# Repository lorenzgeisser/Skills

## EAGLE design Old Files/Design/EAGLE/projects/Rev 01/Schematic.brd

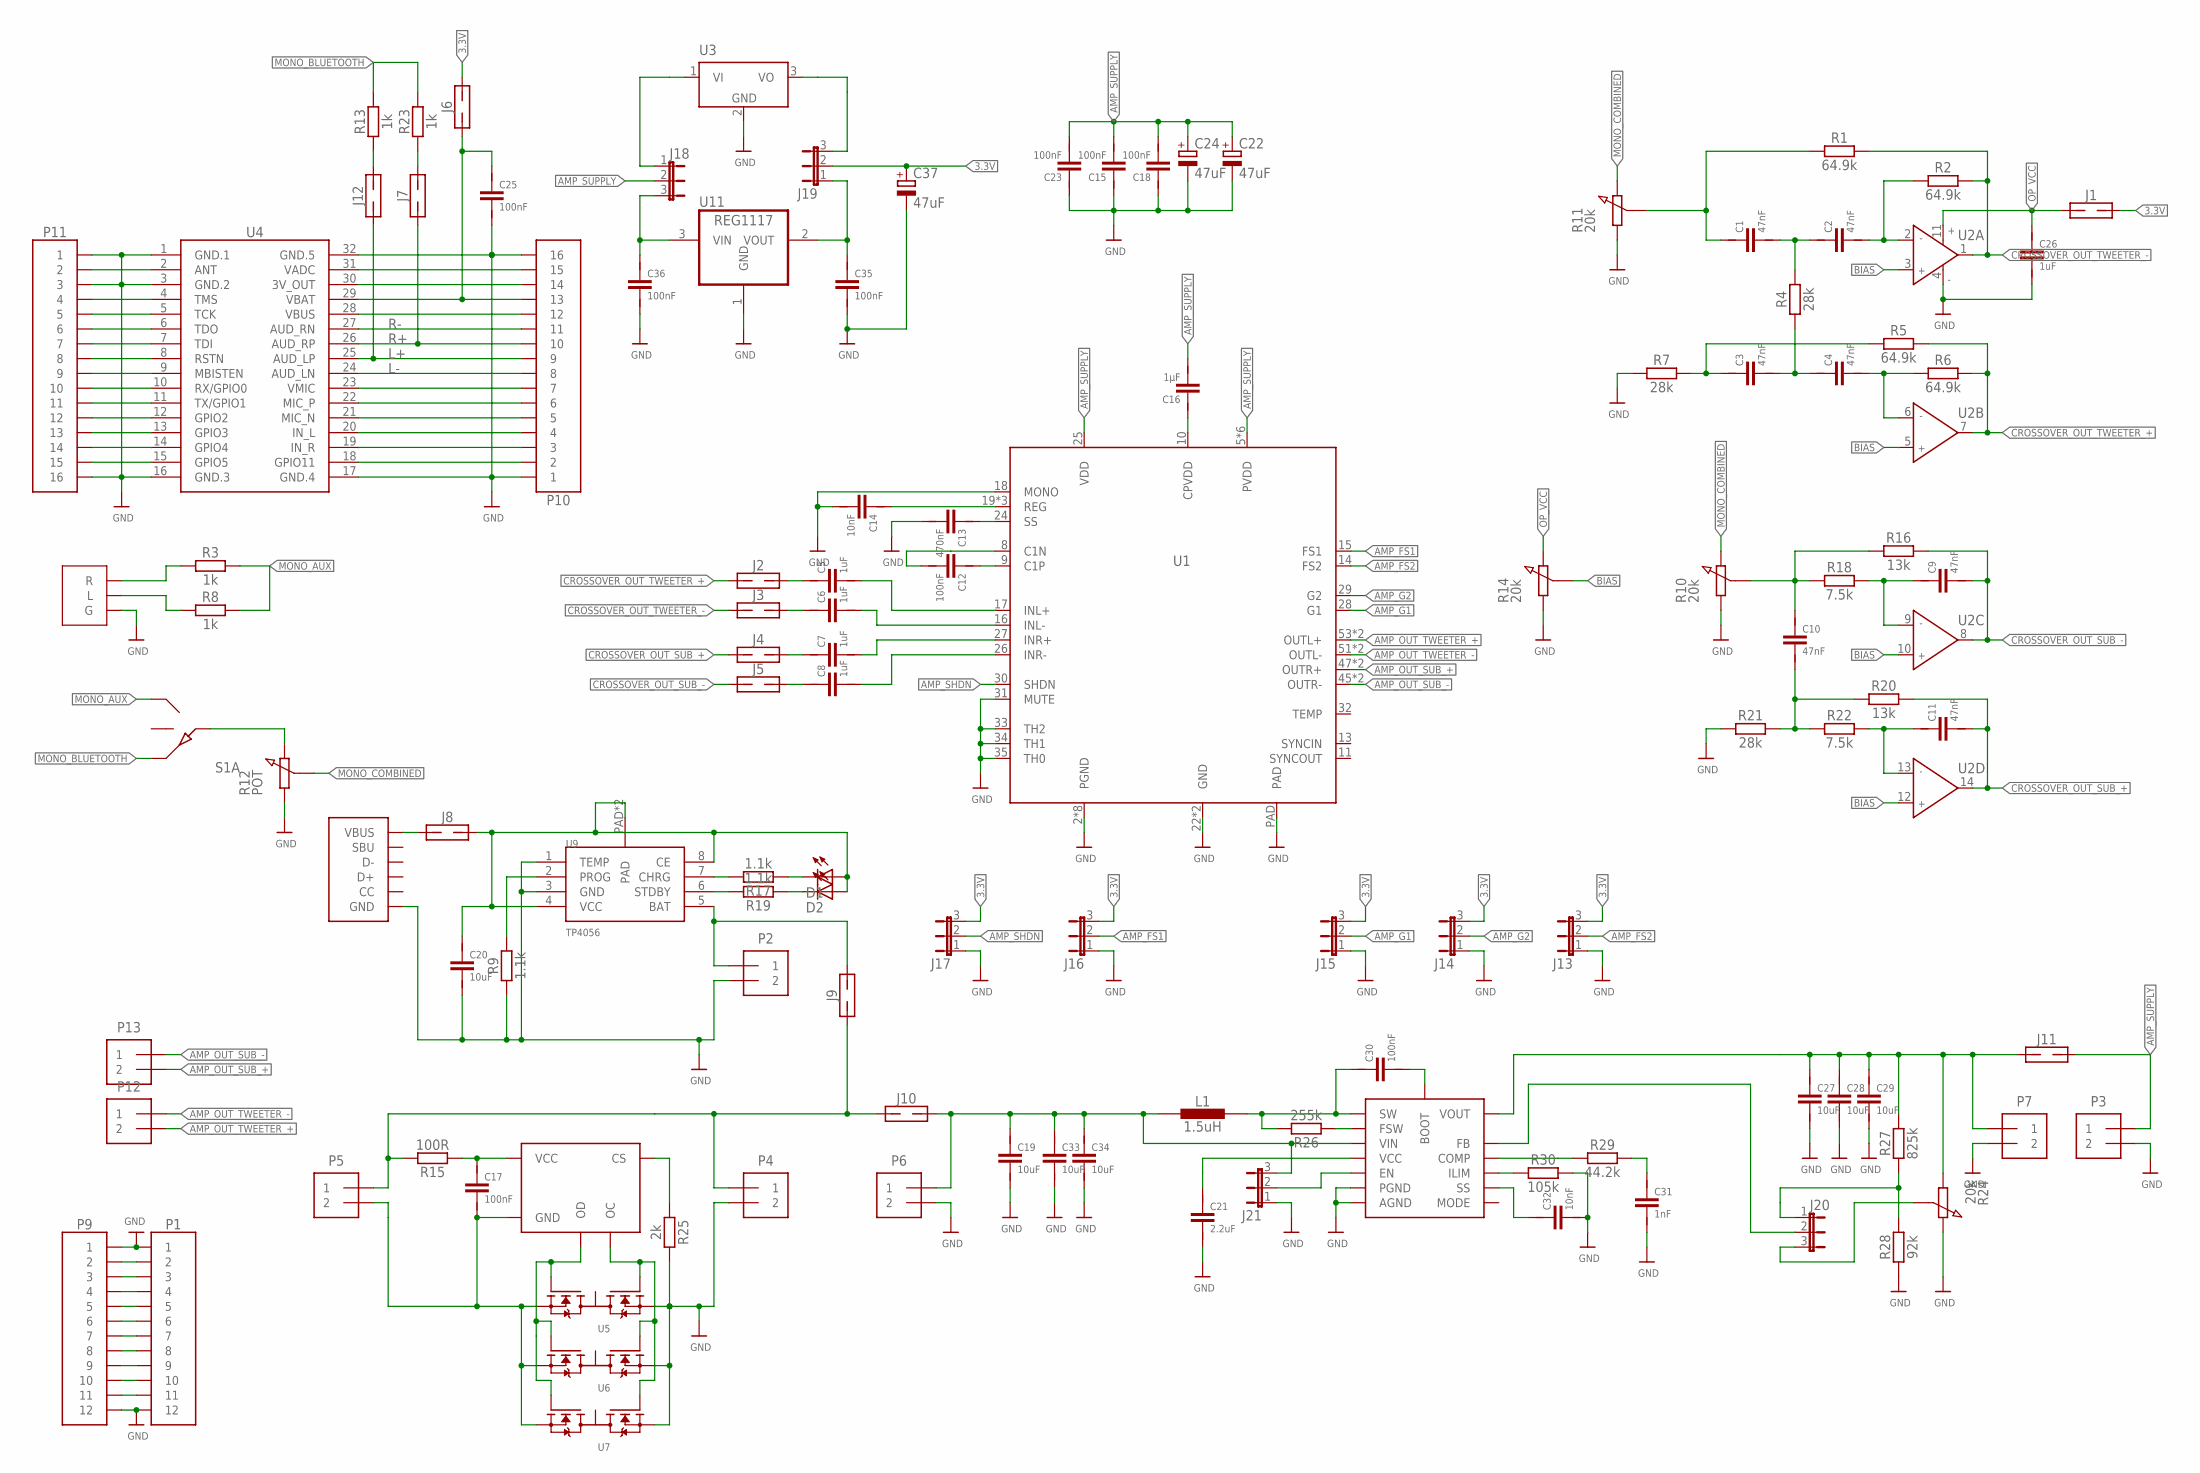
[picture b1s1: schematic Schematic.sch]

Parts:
C1, C2, C3, C4, C9, C10, C11: 47nF; R0603
C5, C6, C7, C8, C26: 1uF; R0603
C12, C15, C17, C18, C23, C25, C30, C35, C36: 100nF; R0603
C13: 470nF; R0603
C14, C32: 10nF; R0603
C16: 1µF; R0603
C19, C20, C27, C28, C29, C33, C34: 10uF; 1206
C21: 2.2uF; R0603
C22, C24, C37: 47uF; E2-4
C31: 1nF; R0603
D1, D2: LEDCHIPLED_0805; CHIPLED_0805
J1, J2, J3, J4, J5, J6, J7, J8, J9, J10, J11, J12: JUMPER_2; PIN_HEADER_2_2
J13, J14, J15, J16, J17, J18, J19, J20, J21: JP2E; JP2
L1: 1.5uH; INDUCTOR2345
P1: TYPE-_BREAKOUT; TYPE-C
P2, P3, P4, P5, P6, P7, P12, P13: HEADER_2TERM; SCREW_TERMINAL_2P
P8: AUX; AUDIO
P9: HEADER_12
P10, P11: HEADER_16
P14: TYPE-C
R1, R2, R5, R6: 64.9k; R0603
R3, R8, R13, R23: 1k; R0603
R4, R7, R21: 28k; R0603
R9, R17, R19: 1.1k; R0603
R10, R11, R14, R24: 20k; TRIMMER
R12: POT
R15: 100R; R0603
R16, R20: 13k; R0603
R18, R22: 7.5k; R0603
R25: 2k; R0603
R26: 255k; R0603
R27: 825k; R0603
R28: 92k; R0603
R29: 44.2k; R0603
R30: 105k; R0603
S1: SWITCH; FE06
U1: MAX9709; TQFN-EP
U2: MAX4478; TSSOP-14
U3: TSR12433; TSR1
U4: WIRELESS-BLUETOOTH-BK8000
U5, U6, U7: FS8205; SOP65P640X120-8N
U8: FS312F; TSOT23-6
U9: TP4056; SOP-8
U10: TPS61088; QFN50P450X350X100-21N
U11: REG1117; SOT223

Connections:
3.3V: C37.+, J1.2, J6.2, J13.3, J14.3, J15.3, J16.3, J17.3, J19.2
AMP_FS1: J16.2, U1.15 (FS1)
AMP_FS2: J13.2, U1.14 (FS2)
AMP_G1: J15.2, U1.28 (G1)
AMP_G2: J14.2, U1.29 (G2)
AMP_OUT_SUB_+: P13.P$2 (2), U1.47 (OUTR+), U1.48 (OUTR+)
AMP_OUT_SUB_-: P13.P$1 (1), U1.45 (OUTR-), U1.46 (OUTR-)
AMP_OUT_TWEETER_+: P12.P$2 (2), U1.53 (OUTL+), U1.54 (OUTL+)
AMP_OUT_TWEETER_-: P12.P$1 (1), U1.51 (OUTL-), U1.52 (OUTL-)
AMP_SHDN: J17.2, U1.30 (SHDN)
AMP_SUPPLY: C15.2, C16.2, C18.2, C22.+, C23.2, C24.+, J11.2, J18.2, P3.P$1 (1), U1.5 (PVDD), U1.6 (PVDD), U1.7 (PVDD), U1.25 (VDD), U1.36 (PVDD), U1.37 (PVDD), U1.38 (PVDD)
BIAS: R14.2, U2.3 (IN+), U2.5 (IN+), U2.10 (IN+), U2.12 (IN+)
CROSSOVER_OUT_SUB_+: C11.2, J4.1, R20.2, U2.14 (OUT)
CROSSOVER_OUT_SUB_-: C9.2, J5.1, R16.2, U2.8 (OUT)
CROSSOVER_OUT_TWEETER_+: J2.1, R5.2, R6.2, U2.7 (OUT)
CROSSOVER_OUT_TWEETER_-: J3.1, R1.2, R2.2, U2.1 (OUT)
GND: C13.2, C14.2, C15.1, C18.1, C19.2, C20.2, C21.2, C22.-, C23.1, C24.-, C25.2, C26.2, C27.2, C28.2, C29.2, C31.2, C32.2, C33.2, C34.2, C35.2, C36.2, C37.-, J13.1, J14.1, J15.1, J16.1, J17.1, J21.1, P1.A1/B12 (1), P1.B1/A12 (12), P1.P$1 (1), P1.P$2 (1), P1.P$3 (1), P1.P$4 (1), P1.P$5 (1), P1.P$6 (1), P1.P$7 (1), P1.P$8 (1), P1.P$9 (1), P1.P$10 (1), P1.P$11 (1), P1.P$12 (1), P1.P$13 (1), P1.P$14 (1), P1.P$15 (1), P1.P$16 (1), P1.P$17 (1), P1.P$18 (1), P1.P$19 (1), P1.P$20 (1), P1.P$21 (1), P1.P$22 (1), P1.P$23 (1), P1.P$24 (1), P1.P$25 (1), P1.P$26 (1), P1.P$27 (1), P1.P$28 (1), P1.P$29 (1), P1.P$30 (1), P1.P$31 (1), P1.P$32 (1), P1.P$33 (1), P1.P$34 (1), P1.P$35 (1), P1.P$36 (1), P1.P$37 (1), P1.P$38 (1), P2.P$2 (2), P3.P$2 (2), P4.P$2 (2), P6.P$2 (2), P7.P$2 (2), P8.P$3 (G), P9.1, P9.12, P10.1, P10.16, P11.1, P11.3, P11.16, P14.A1/B12 (GND), P14.B1/A12 (GND), P14.P$1 (GND), P14.P$2 (GND), P14.P$3 (GND), P14.P$4 (GND), P14.P$5 (GND), P14.P$6 (GND), P14.P$7 (GND), P14.P$8 (GND), P14.P$9 (GND), P14.P$10 (GND), P14.P$11 (GND), P14.P$12 (GND), P14.P$13 (GND), P14.P$14 (GND), P14.P$15 (GND), P14.P$16 (GND), P14.P$17 (GND), P14.P$18 (GND), P14.P$19 (GND), P14.P$20 (GND), P14.P$21 (GND), P14.P$22 (GND), P14.P$23 (GND), P14.P$24 (GND), P14.P$25 (GND), P14.P$26 (GND), P14.P$27 (GND), P14.P$28 (GND), P14.P$29 (GND), P14.P$30 (GND), P14.P$31 (GND), P14.P$32 (GND), P14.P$33 (GND), P14.P$34 (GND), P14.P$35 (GND), P14.P$36 (GND), P14.P$37 (GND), P14.P$38 (GND), R7.1, R9.1, R10.1, R11.1, R12.1, R14.1, R21.1, R24.3, R25.2, R28.1, R30.2, U1.2 (PGND), U1.3 (PGND), U1.4 (PGND), U1.18 (MONO), U1.22 (GND), U1.23 (GND), U1.31 (MUTE), U1.33 (TH2), U1.34 (TH1), U1.35 (TH0), U1.39 (PGND), U1.40 (PGND), U1.41 (PGND), U1.49 (PGND), U1.50 (PGND), U1.PAD, U2.4 (-), U3.2 (GND), U4.1 (GND.1), U4.3 (GND.2), U4.16 (GND.3), U4.17 (GND.4), U4.32 (GND.5), U5.6 (S2), U5.7 (S2), U6.6 (S2), U6.7 (S2), U7.6 (S2), U7.7 (S2), U9.1 (TEMP), U9.3 (GND), U10.20 (AGND), U10.21 (PGND), U10.22 (PGND), U11.1 (GND)
L+: J12.1, P10.9, U4.25 (AUD_LP)
L-: P10.8, U4.24 (AUD_LN)
MONO_AUX: R3.2, R8.2, S1.P$1 (1)
MONO_BLUETOOTH: R13.2, R23.2, S1.P$3 (3)
MONO_COMBINED: R10.3, R11.3, R12.2
unnamed: C5.1, J2.2
unnamed: C1.2, C2.1, R4.2
unnamed: C2.2, R2.1, U2.2 (IN-)
unnamed: C1.1, R1.1, R11.2
unnamed: C27.1, C28.1, C29.1, J11.1, P7.P$1 (1), R24.1, R27.2, U10.14 (VOUT), U10.15 (VOUT), U10.16 (VOUT)
unnamed: C4.2, R6.1, U2.6 (IN-)
unnamed: C3.2, C4.1, R4.1
unnamed: C3.1, R5.1, R7.2
unnamed: C6.1, J3.2
unnamed: C9.1, R18.2, U2.9 (IN-)
unnamed: C7.1, J4.2
unnamed: C11.1, R22.2, U2.13 (IN-)
unnamed: C10.1, R10.2, R16.1, R18.1
unnamed: C10.2, R20.1, R21.2, R22.1
unnamed: C8.1, J5.2
unnamed: C6.2, U1.16 (INL-)
unnamed: C36.1, J18.3, U11.3 (VIN)
unnamed: P8.P$1 (L), R8.1
unnamed: P8.P$2 (R), R3.1
unnamed: R12.3, S1.P$5 (C)
unnamed: C7.2, U1.27 (INR+)
unnamed: C8.2, U1.26 (INR-)
unnamed: C5.2, U1.17 (INL+)
unnamed: C12.2, U1.8 (C1N)
unnamed: C12.1, U1.9 (C1P)
unnamed: C13.1, U1.24 (SS)
unnamed: P1.A4/B9 (2), P9.2
unnamed: C14.1, U1.19 (REG), U1.20 (REG), U1.21 (REG)
unnamed: P1.B8 (3), P9.3
unnamed: P1.A5 (4), P9.4
unnamed: P1.B7 (5), P9.5
unnamed: P1.A6 (6), P9.6
unnamed: P1.A7 (7), P9.7
unnamed: C16.1, U1.10 (CPVDD)
unnamed: U5.5 (G2), U6.5 (G2), U7.5 (G2), U8.3 (OC)
unnamed: C20.1, D1.A, D2.A, J8.2, U9.4 (VCC), U9.8 (CE), U9.PAD, U9.PAD2 (PAD)
unnamed: R9.2, U9.2 (PROG)
unnamed: J19.3, U3.3 (VO)
unnamed: R17.2, U9.7 (CHRG)
unnamed: R19.2, U9.6 (STDBY)
unnamed: D1.C, R17.1
unnamed: D2.C, R19.1
unnamed: J9.2, P2.P$1 (1), U9.5 (BAT)
unnamed: J8.1, P14.A4/B9 (VBUS), P14.B4/A9 (VBUS)
unnamed: R26.1, U10.3 (FSW)
unnamed: P1.B6 (8), P9.8
unnamed: P1.A8 (9), P9.9
unnamed: P1.B5 (10), P9.10
unnamed: P1.B4/A9 (11), P9.11
unnamed: C35.1, J19.1, U11.2 (VOUT)
unnamed: R25.1, U8.2 (CS)
unnamed: C17.1, R15.1, U8.5 (VCC)
unnamed: C17.2, P5.P$2 (2), U5.2 (S1), U5.3 (S1), U6.2 (S1), U6.3 (S1), U7.2 (S1), U7.3 (S1), U8.6 (GND)
unnamed: J9.1, J10.1, P4.P$1 (1), P5.P$1 (1), R15.2
unnamed: U5.4 (G1), U6.4 (G1), U7.4 (G1), U8.1 (OD)
unnamed: C30.1, L1.P$2 (2), R26.2, U10.4 (SW), U10.5 (SW), U10.6 (SW), U10.7 (SW)
unnamed: C30.2, U10.8 (BOOT)
unnamed: C21.1, U10.1 (VCC)
unnamed: C19.1, C33.1, C34.1, J10.2, J21.3, L1.P$1 (1), P6.P$1 (1), U10.9 (VIN)
unnamed: J21.2, U10.2 (EN)
unnamed: R30.1, U10.19 (ILIM)
unnamed: R29.1, U10.18 (COMP)
unnamed: C31.1, R29.2
unnamed: J20.2, U10.17 (FB)
unnamed: C32.1, U10.10 (SS)
unnamed: J20.1, R27.1, R28.2
unnamed: J20.3, R24.2
unnamed: P10.2, U4.18 (GPIO11)
unnamed: P10.3, U4.19 (IN_R)
unnamed: P10.4, U4.20 (IN_L)
unnamed: P10.5, U4.21 (MIC_N)
unnamed: P10.6, U4.22 (MIC_P)
unnamed: P10.7, U4.23 (VMIC)
unnamed: P10.12, U4.28 (VBUS)
unnamed: C25.1, J6.1, P10.13, U4.29 (VBAT)
unnamed: P10.14, U4.30 (3V_OUT)
unnamed: P10.15, U4.31 (VADC)
unnamed: P11.2, U4.2 (ANT)
unnamed: P11.4, U4.4 (TMS)
unnamed: P11.5, U4.5 (TCK)
unnamed: P11.6, U4.6 (TDO)
unnamed: P11.7, U4.7 (TDI)
unnamed: P11.8, U4.8 (RSTN)
unnamed: P11.9, U4.9 (MBISTEN)
unnamed: P11.10, U4.10 (RX/GPIO0)
unnamed: P11.11, U4.11 (TX/GPIO1)
unnamed: P11.12, U4.12 (GPIO2)
unnamed: P11.13, U4.13 (GPIO3)
unnamed: P11.14, U4.14 (GPIO4)
unnamed: P11.15, U4.15 (GPIO5)
unnamed: J7.2, R23.1
unnamed: J12.2, R13.1
OP_VCC: C26.1, J1.1, R14.3, U2.11 (+)
R+: J7.1, P10.10, U4.26 (AUD_RP)
R-: P10.11, U4.27 (AUD_RN)
VI: J18.1, U3.1 (VI)

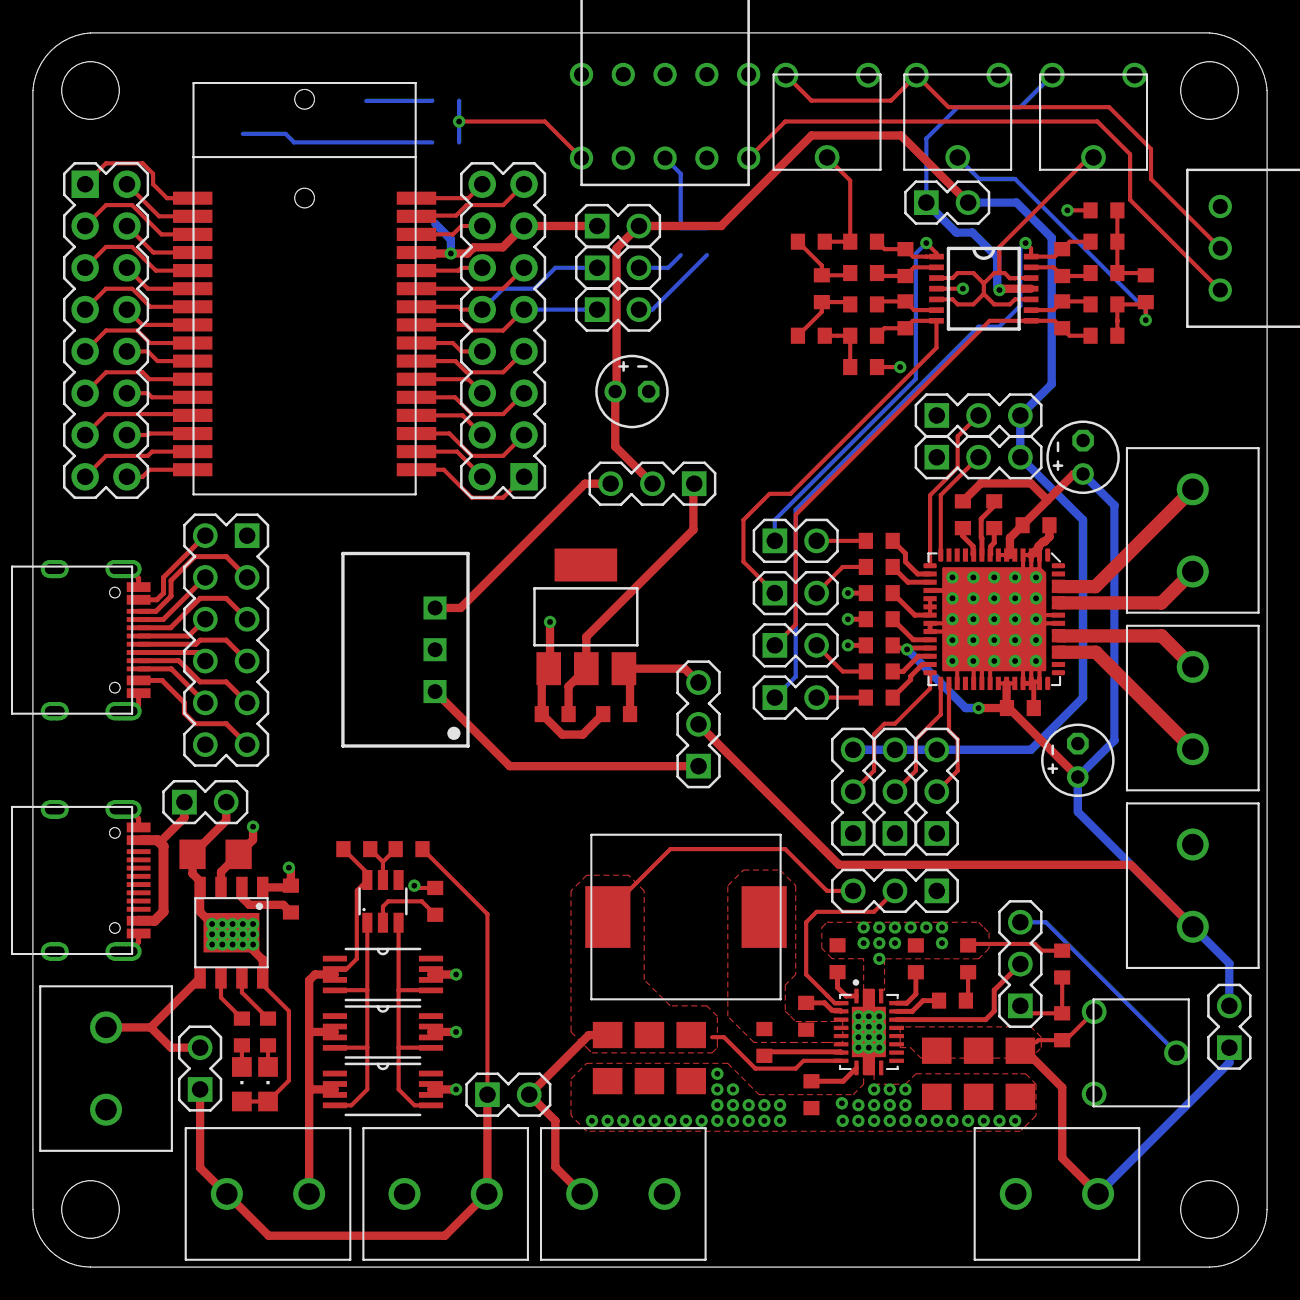
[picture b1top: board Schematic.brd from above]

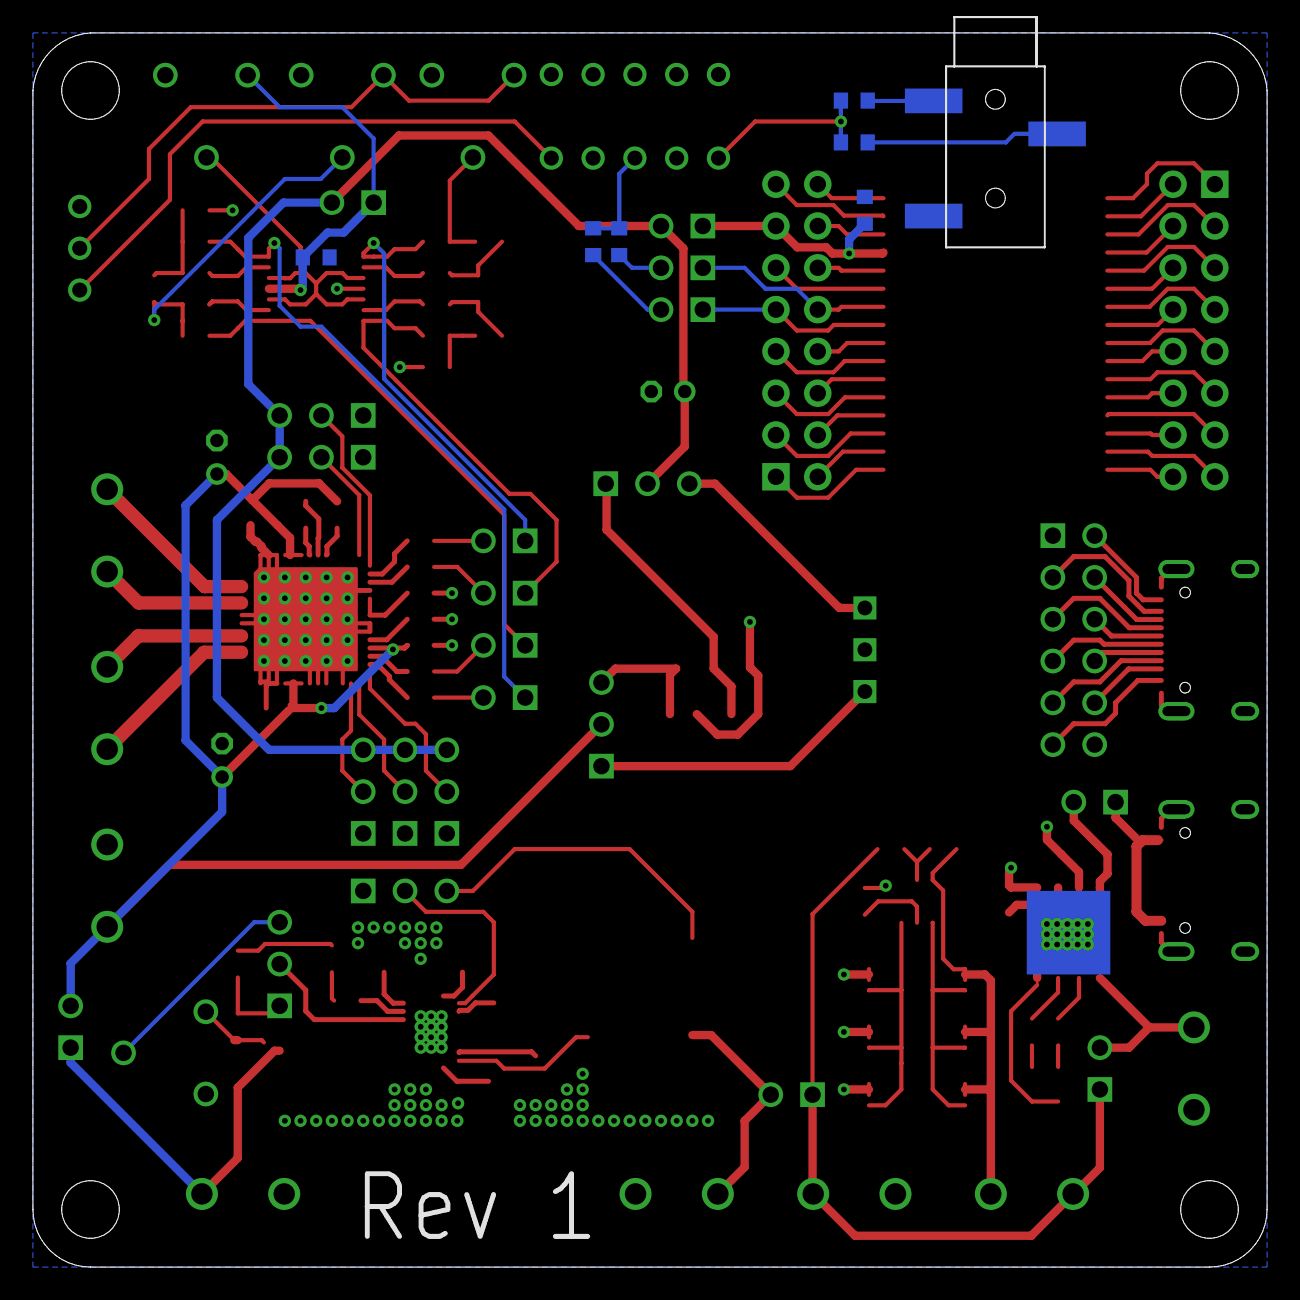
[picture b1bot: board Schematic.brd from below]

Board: 2 copper layers, 75.0 x 75.0 mm, 117 parts (7 on the bottom side), 118 nets.

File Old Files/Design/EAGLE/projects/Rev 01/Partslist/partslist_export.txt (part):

Partlist

Exported from Schematic.sch at 8/4/2018 7:06 PM

EAGLE Version 9.1.1 Copyright (c) 1988-2018 Autodesk, Inc.

Assembly variant: 

Part     Value                     Device                    Package                   Library    Sheet

C1       47nF                      CAPACITOR                 R0603                     Schematic  1
C2       47nF                      CAPACITOR                 R0603                     Schematic  1
C3       47nF                      CAPACITOR                 R0603                     Schematic  1
C4       47nF                      CAPACITOR                 R0603                     Schematic  1
C5       1uF                       CAPACITOR                 R0603                     Schematic  1
C6       1uF                       CAPACITOR                 R0603                     Schematic  1
C7       1uF                       CAPACITOR                 R0603                     Schematic  1
C8       1uF                       CAPACITOR                 R0603                     Schematic  1
C9       47nF                      CAPACITOR                 R0603                     Schematic  1
C10      47nF                      CAPACITOR                 R0603                     Schematic  1
C11      47nF                      CAPACITOR                 R0603                     Schematic  1
C12      100nF                     CAPACITOR                 R0603                     Schematic  1
C13      470nF                     CAPACITOR                 R0603                     Schematic  1
C14      10nF                      CAPACITOR                 R0603                     Schematic  1
C15      100nF                     CAPACITOR                 R0603                     Schematic  1
C16      1µF                       CAPACITOR                 R0603                     Schematic  1
C17      100nF                     CAPACITOR                 R0603                     Schematic  1
C18      100nF                     CAPACITOR                 R0603                     Schematic  1
C19      10uF                      CAPACITOR1206             1206                      Schematic  1
C20      10uF                      CAPACITOR1206             1206                      Schematic  1
C21      2.2uF                     CAPACITOR                 R0603                     Schematic  1
C22      47uF                      CPOL-EUE2-4               E2-4                      Schematic  1
C23      100nF                     CAPACITOR                 R0603                     Schematic  1
C24      47uF                      CPOL-EUE2-4               E2-4                      Schematic  1
C25      100nF                     CAPACITOR                 R0603                     Schematic  1
C26      1uF                       CAPACITOR                 R0603                     Schematic  1
C27      10uF                      CAPACITOR1206             1206                      Schematic  1
C28      10uF                      CAPACITOR1206             1206                      Schematic  1
C29      10uF                      CAPACITOR1206             1206                      Schematic  1
C30      100nF                     CAPACITOR                 R0603                     Schematic  1
C31      1nF                       CAPACITOR                 R0603                     Schematic  1
C32      10nF                      CAPACITOR                 R0603                     Schematic  1
C33      10uF                      CAPACITOR1206             1206                      Schematic  1
C34      10uF                      CAPACITOR1206             1206                      Schematic  1
C35      100nF                     CAPACITOR                 R0603                     Schematic  1
C36      100nF                     CAPACITOR                 R0603                     Schematic  1
C37      47uF                      CPOL-EUE2-4               E2-4                      Schematic  1
D1                                 LEDCHIPLED_0805           CHIPLED_0805              Schematic  1
D2                                 LEDCHIPLED_0805           CHIPLED_0805              Schematic  1
J1       JUMPER_2                  JUMPER_2                  PIN_HEADER_2_2            Schematic  1
J2       JUMPER_2                  JUMPER_2                  PIN_HEADER_2_2            Schematic  1
J3       JUMPER_2                  JUMPER_2                  PIN_HEADER_2_2            Schematic  1
J4       JUMPER_2                  JUMPER_2                  PIN_HEADER_2_2            Schematic  1
J5       JUMPER_2                  JUMPER_2                  PIN_HEADER_2_2            Schematic  1
J6       JUMPER_2                  JUMPER_2                  PIN_HEADER_2_2            Schematic  1
J7       JUMPER_2                  JUMPER_2                  PIN_HEADER_2_2            Schematic  1
J8       JUMPER_2                  JUMPER_2                  PIN_HEADER_2_2            Schematic  1
J9       JUMPER_2                  JUMPER_2                  PIN_HEADER_2_2            Schematic  1
J10      JUMPER_2                  JUMPER_2                  PIN_HEADER_2_2            Schematic  1
J11      JUMPER_2                  JUMPER_2                  PIN_HEADER_2_2            Schematic  1
J12      JUMPER_2                  JUMPER_2                  PIN_HEADER_2_2            Schematic  1
J13                                JP2E                      JP2                       Schematic  1
J14                                JP2E                      JP2                       Schematic  1
J15                                JP2E                      JP2                       Schematic  1
J16                                JP2E                      JP2                       Schematic  1
J17                                JP2E                      JP2                       Schematic  1
J18                                JP2E                      JP2                       Schematic  1
J19                                JP2E                      JP2                       Schematic  1
J20                                JP2E                      JP2                       Schematic  1
J21                                JP2E                      JP2                       Schematic  1
L1       1.5uH                     INDUCTOR6519              INDUCTOR2345              Schematic  1
P1       TYPE-_BREAKOUT            TYPE-_BREAKOUT            TYPE-C                    Schematic  1
P2       HEADER_2TERM              HEADER_2TERM              SCREW_TERMINAL_2P         Schematic  1
P3       HEADER_2TERM              HEADER_2TERM              SCREW_TERMINAL_2P         Schematic  1
P4       HEADER_2TERM              HEADER_2TERM              SCREW_TERMINAL_2P         Schematic  1
P5       HEADER_2TERM              HEADER_2TERM              SCREW_TERMINAL_2P         Schematic  1
P6       HEADER_2TERM              HEADER_2TERM              SCREW_TERMINAL_2P         Schematic  1
P7       HEADER_2TERM              HEADER_2TERM              SCREW_TERMINAL_2P         Schematic  1
P8       AUX                       AUX                       AUDIO                     Schematic  1
P9       HEADER_12                 HEADER_12                 HEADER_12                 Schematic  1
P10      HEADER_16                 HEADER_16                 HEADER_16                 Schematic  1
P11      HEADER_16                 HEADER_16                 HEADER_16                 Schematic  1
P12      HEADER_2TERM              HEADER_2TERM              SCREW_TERMINAL_2P         Schematic  1
P13      HEADER_2TERM              HEADER_2TERM              SCREW_TERMINAL_2P         Schematic  1
P14      TYPE-C                    TYPE-C                    TYPE-C                    Schematic  1
R1       64.9k                     RESISTOR0603              R0603                     Schematic  1
R2       64.9k                     RESISTOR0603              R0603                     Schematic  1
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
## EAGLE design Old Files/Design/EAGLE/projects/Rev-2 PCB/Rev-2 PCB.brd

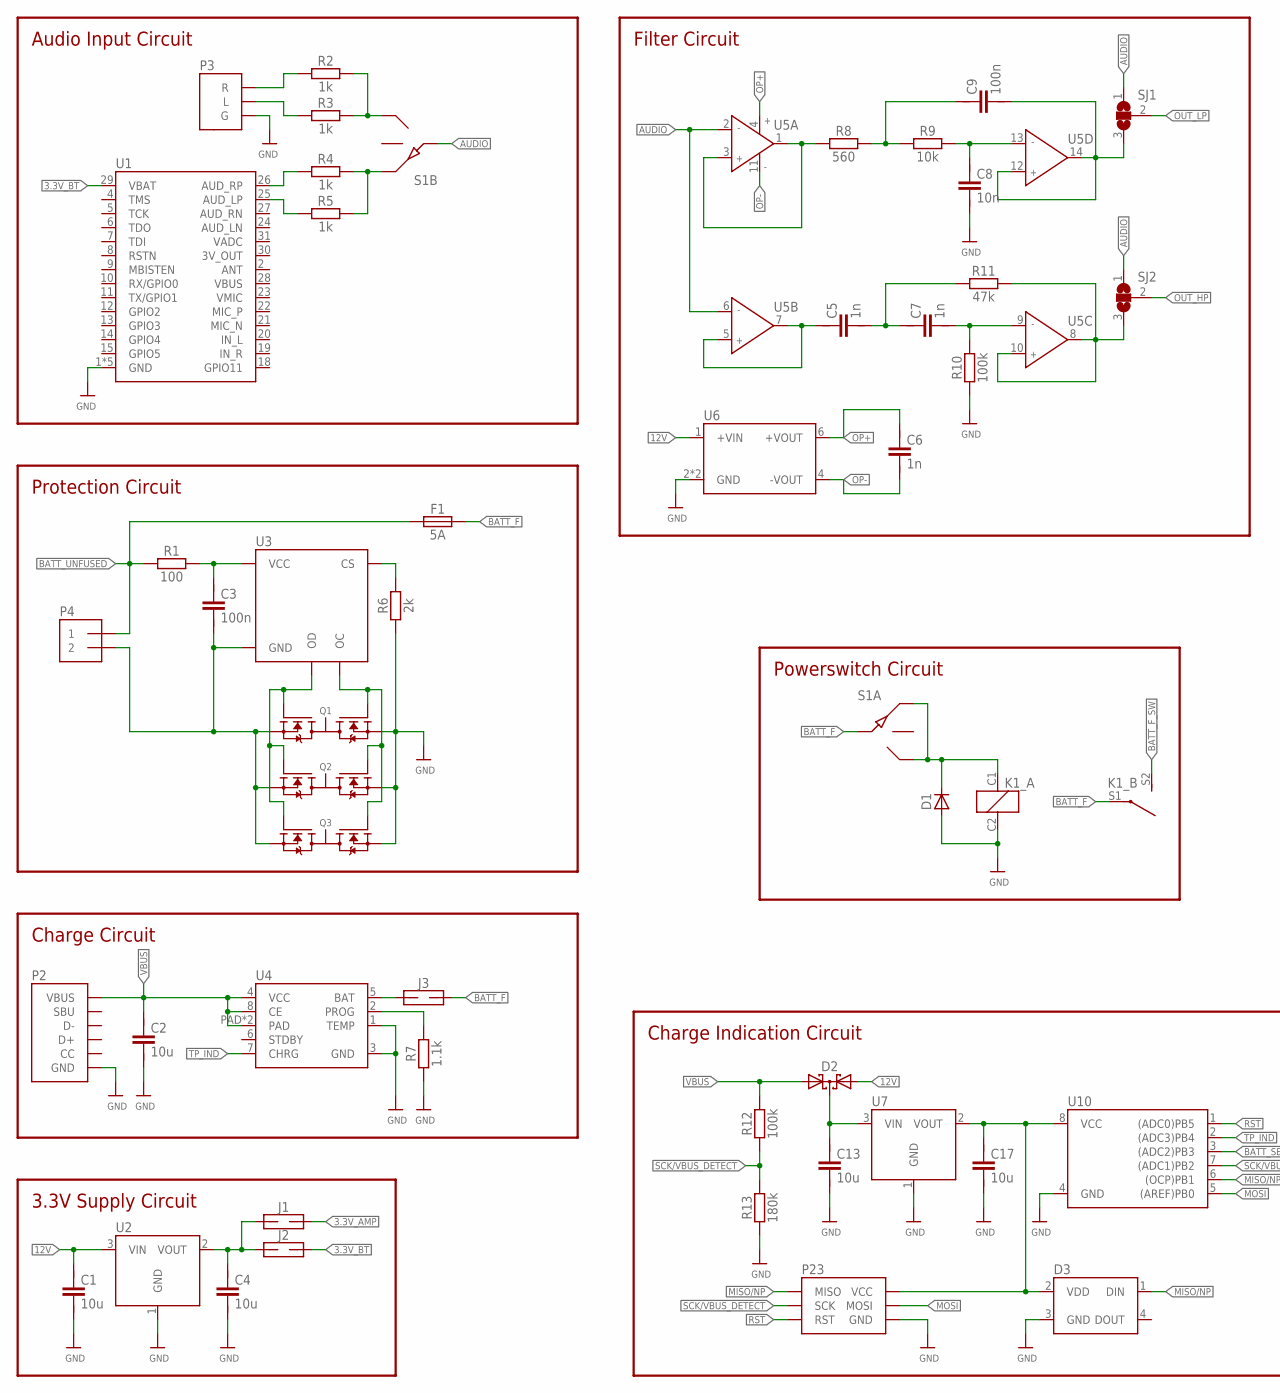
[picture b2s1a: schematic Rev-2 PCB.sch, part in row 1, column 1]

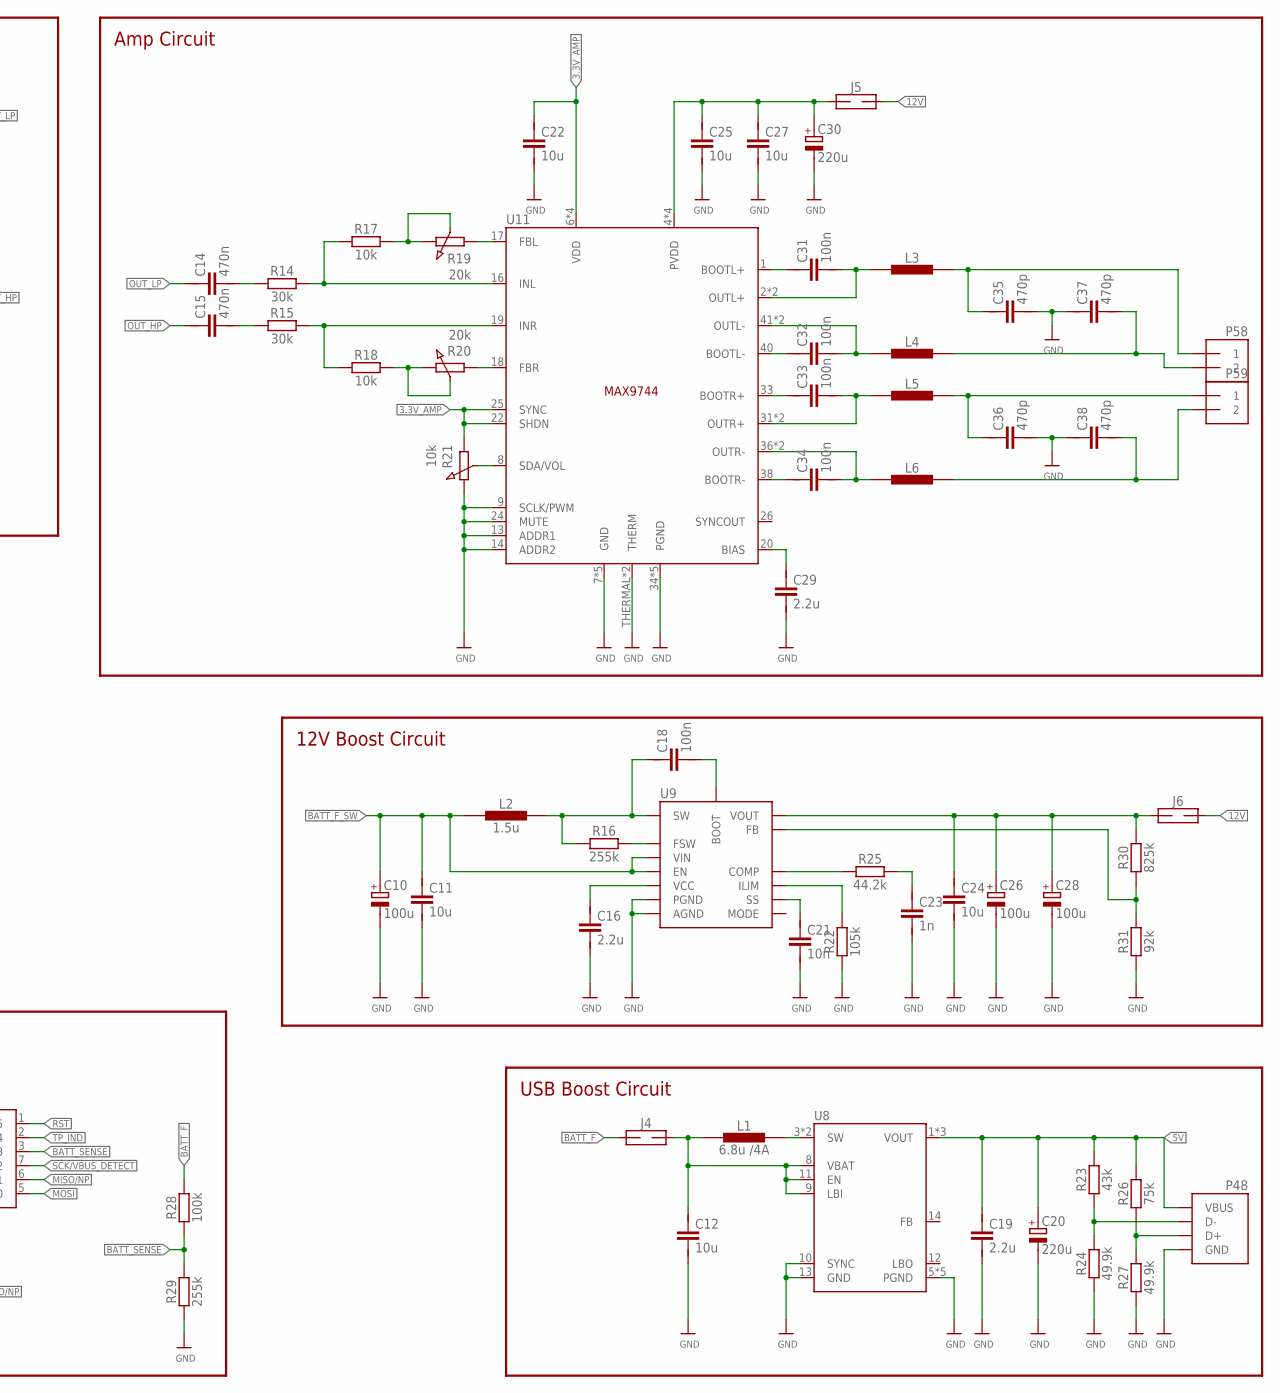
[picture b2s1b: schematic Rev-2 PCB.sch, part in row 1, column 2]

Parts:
C1, C4, C13, C17: 10u; R0603
C2, C11, C12, C22, C24, C25, C27: 10u; 1206
C3, C9, C18: 100n; R0603
C5, C6, C7, C23: 1n; R0603
C8, C21: 10n; R0603
C10, C26, C28: 100u; UD-6,3X7,7_NICHICON
C14, C15: 470n; R0603
C16, C19, C29: 2.2u; R0603
C20, C30: 220u; UD-6,3X7,7_NICHICON
C31, C32, C33, C34: 100n; 0805
C35, C36, C37, C38: 470p; 0805
D1: DIODEDO-214AC; DO214AC
D2: BAS70-05; SOT23
D3: NEOPIXEL; LED-RGB-THRU
F1: 5A; FUSE_SMD
J1, J2, J3, J4, J5, J6: JUMPER_2S; SJ
K1: RELAY_2; RELAY
L1: 6.8u /4A; INDUCTOR234545
L2: 1.5u; INDUCTOR2345
L3, L4, L5, L6: INDUCTOR0805; 0805
P2: USB_TYPE-C; TYPE-C
P3: AUX; AUDIO
P4, P58, P59: HEADER_2MOLEX; MOLEX_43650_2P
P23: SPI-HEADERNS; 2X3-NS
P48: USB_TYPE-A; USB-A
Q1, Q2, Q3: FS8205; SOP65P640X120-8N
R1: 100; R0603
R2, R3, R4, R5: 1k; R0603
R6: 2k; R0603
R7: 1.1k; R0603
R8: 560; R0603
R9, R17, R18: 10k; R0603
R10, R12, R28: 100k; R0603
R11: 47k; R0603
R13: 180k; R0603
R14, R15: 30k; R0603
R16, R29: 255k; R0603
R19, R20: 20k; TRIMMPOTI
R21: 10k; POT
R22: 105k; R0603
R23: 43k; R0603
R24, R27: 49.9k; R0603
R25: 44.2k; R0603
R26: 75k; R0603
R30: 825k; R0603
R31: 92k; R0603
S1: SWITCH; FE06
SJ1, SJ2: SJ2W; SJ_2
U1: BK8000; WIRELESS-BLUETOOTH-BK8000
U2, U7: REG1118SOT23-3; SOT23
U3: FS312F; TSOT23-6
U4: TP4056; SOP-8
U5: QUAD_OP; SO14
U6: NMA; CONV_PCN2-S24-D15-S
U8: TPS6103X; PVQFN-16
U9: TPS61088; QFN50P450X350X100-21N
U10: TINY15LS; SOIC8
U11: MAX9744; TQFN44_7MM

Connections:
3.3V_AMP: C22.1, J1.2, R21.1, U11.6 (VDD), U11.10 (VDD), U11.21 (VDD), U11.22 (SHDN), U11.25 (SYNC), U11.28 (VDD)
3.3V_BT: J2.2, U1.29 (VBAT)
3V_OUT: U1.30 (3V_OUT)
5V: C19.1, C20.+, P48.VBUS, R23.2, R26.2, U8.1 (VOUT), U8.15 (VOUT), U8.16 (VOUT)
12V: C1.1, D2.1 (A1), J5.2, J6.2, U2.3 (VIN), U6.1 (+VIN)
12V_AMP: C25.1, C27.1, C30.+, J5.1, U11.4 (PVDD), U11.5 (PVDD), U11.29 (PVDD), U11.30 (PVDD)
AUDIO: S1.P$6 (C), SJ1.1, SJ2.1, U5.2 (IN-), U5.6 (IN-)
BATT_F: F1.2 (4), J3.2, J4.1, K1.S1 (MITTE), R28.2, S1.P$5 (C)
BATT_F_SW: C10.+, C11.1, K1.S2 (OFF), L2.P$1 (1), U9.2 (EN), U9.9 (VIN)
BATT_SENSE: R28.1, R29.2, U10.3 ((ADC2)PB3)
BATT_UNFUSED: F1.1 (3), P4.1, R1.1
GND: C1.2, C2.2, C4.2, C8.2, C10.-, C11.2, C12.2, C13.2, C16.2, C17.2, C19.2, C20.-, C21.2, C22.2, C23.2, C24.2, C25.2, C26.-, C27.2, C28.-, C29.2, C30.-, C35.2, C36.2, C37.1, C38.1, D1.A, D3.3 (GND), K1.C2 (2), P2.A1/B12 (GND), P2.B1/A12 (GND), P2.P$1 (GND), P2.P$2 (GND), P2.P$3 (GND), P2.P$4 (GND), P2.P$5 (GND), P2.P$6 (GND), P2.P$7 (GND), P2.P$8 (GND), P2.P$9 (GND), P2.P$10 (GND), P2.P$11 (GND), P2.P$12 (GND), P2.P$13 (GND), P2.P$14 (GND), P2.P$15 (GND), P2.P$16 (GND), P2.P$17 (GND), P2.P$18 (GND), P2.P$19 (GND), P2.P$20 (GND), P2.P$21 (GND), P2.P$22 (GND), P2.P$23 (GND), P2.P$24 (GND), P2.P$25 (GND), P2.P$26 (GND), P2.P$27 (GND), P2.P$28 (GND), P2.P$29 (GND), P2.P$30 (GND), P2.P$31 (GND), P2.P$32 (GND), P2.P$33 (GND), P2.P$34 (GND), P2.P$35 (GND), P2.P$36 (GND), P2.P$37 (GND), P2.P$38 (GND), P3.P$3 (G), P23.6 (GND), P48.GND, P48.S1 (GND), P48.S2 (GND), P48.S3 (GND), P48.S4 (GND), Q1.6 (S2), Q1.7 (S2), Q2.6 (S2), Q2.7 (S2), Q3.6 (S2), Q3.7 (S2), R6.1, R7.1, R10.1, R13.1, R21.3, R22.1, R24.1, R27.1, R29.1, R31.1, U1.1 (GND), U1.3 (GND), U1.16 (GND), U1.17 (GND), U1.32 (GND), U2.1 (GND), U4.1 (TEMP), U4.3 (GND), U6.2 (GND), U6.5 (GND), U7.1 (GND), U8.5 (PGND), U8.6 (PGND), U8.7 (PGND), U8.10 (SYNC), U8.13 (GND), U8.THERMAL (PGND), U8.THERMAL1 (PGND), U9.20 (AGND), U9.21 (PGND), U9.22 (PGND), U9.23 (PGND), U10.4 (GND), U11.7 (GND), U11.9 (SCLK/PWM), U11.11 (GND), U11.12 (GND), U11.13 (ADDR1), U11.14 (ADDR2), U11.15 (GND), U11.24 (MUTE), U11.27 (GND), U11.34 (PGND), U11.35 (PGND), U11.39 (PGND), U11.43 (PGND), U11.44 (PGND), U11.THERMAL (THERM), U11.THERMAL1 (THERM)
MISO/NP: D3.1 (DIN), P23.1 (MISO), U10.6 ((OCP)PB1)
MOSI: P23.4 (MOSI), U10.5 ((AREF)PB0)
unnamed: C3.2, P4.2, Q1.2 (S1), Q1.3 (S1), Q2.2 (S1), Q2.3 (S1), Q3.2 (S1), Q3.3 (S1), U3.6 (GND)
unnamed: C3.1, R1.2, U3.5 (VCC)
unnamed: R6.2, U3.2 (CS)
unnamed: R8.1, U5.1 (OUT), U5.3 (IN+)
unnamed: Q1.4 (G1), Q2.4 (G1), Q3.4 (G1), U3.1 (OD)
unnamed: C13.1, D2.3 (C), U7.3 (VIN)
unnamed: Q1.5 (G2), Q2.5 (G2), Q3.5 (G2), U3.3 (OC)
unnamed: R16.2, U9.3 (FSW)
unnamed: C16.1, U9.1 (VCC)
unnamed: C18.2, U9.8 (BOOT)
unnamed: C18.1, L2.P$2 (2), R16.1, U9.4 (SW), U9.5 (SW), U9.6 (SW), U9.7 (SW)
unnamed: R22.2, U9.19 (ILIM)
unnamed: R7.2, U4.2 (PROG)
unnamed: C21.1, U9.10 (SS)
unnamed: R25.1, U9.18 (COMP)
unnamed: C23.1, R25.2
unnamed: L1.P$2 (2), U8.3 (SW), U8.4 (SW)
unnamed: R30.1, R31.2, U9.17 (FB)
unnamed: C4.1, J1.1, J2.1, U2.2 (VOUT)
unnamed: C17.1, D3.2 (VDD), P23.2 (VCC), U7.2 (VOUT), U10.8 (VCC)
unnamed: P48.D+, R26.1, R27.2
unnamed: P48.D-, R23.1, R24.2
unnamed: C12.1, J4.2, L1.P$1 (1), U8.8 (VBAT), U8.9 (LBI), U8.11 (EN)
unnamed: R21.2, U11.8 (SDA/VOL)
unnamed: J3.1, U4.5 (BAT)
unnamed: C9.1, R8.2, R9.1
unnamed: C5.1, U5.5 (IN+), U5.7 (OUT)
unnamed: R4.1, U1.26 (AUD_RP)
unnamed: R5.1, U1.25 (AUD_LP)
unnamed: C8.1, R9.2, U5.13 (IN-)
unnamed: C5.2, C7.1, R11.1
unnamed: C7.2, R10.2, U5.9 (IN-)
unnamed: C24.1, C26.+, C28.+, J6.1, R30.2, U9.14 (VOUT), U9.15 (VOUT), U9.16 (VOUT)
unnamed: R18.2, R20.2, R20.3
unnamed: R17.2, R19.2, R19.3
unnamed: P3.P$1 (L), R3.1
unnamed: R19.1, U11.17 (FBL)
unnamed: D1.C, K1.C1 (1), S1.P$1 (1), S1.P$3 (3)
unnamed: R4.2, R5.2, S1.P$8 (3)
unnamed: R2.2, R3.2, S1.P$10 (1)
unnamed: P3.P$2 (R), R2.1
unnamed: R20.1, U11.18 (FBR)
unnamed: R14.2, R17.1, U11.16 (INL)
unnamed: R15.2, R18.1, U11.19 (INR)
unnamed: C29.1, U11.20 (BIAS)
unnamed: C31.1, U11.1 (BOOTL+)
unnamed: C31.2, L3.1, U11.2 (OUTL+), U11.3 (OUTL+)
unnamed: C14.2, R14.1
unnamed: C15.2, R15.1
unnamed: C32.1, U11.40 (BOOTL-)
unnamed: C32.2, L4.1, U11.41 (OUTL-), U11.42 (OUTL-)
unnamed: C33.1, U11.33 (BOOTR+)
unnamed: C33.2, L5.1, U11.31 (OUTR+), U11.32 (OUTR+)
unnamed: C34.1, U11.38 (BOOTR-)
unnamed: C34.2, L6.1, U11.36 (OUTR-), U11.37 (OUTR-)
unnamed: C35.1, L3.2, P58.1
unnamed: C37.2, L4.2, P58.2
unnamed: C36.1, L5.2, P59.1
unnamed: C38.2, L6.2, P59.2
OP+: C6.1, U5.4 (+), U6.6 (+VOUT)
OP-: C6.2, U5.11 (-), U6.4 (-VOUT)
OUT_HP: C15.1, SJ2.2
OUT_HP_OP: R11.2, SJ2.3, U5.8 (OUT), U5.10 (IN+)
OUT_LP: C14.1, SJ1.2
OUT_LP_OP: C9.2, SJ1.3, U5.12 (IN+), U5.14 (OUT)
RST: P23.5 (RST), U10.1 ((ADC0)PB5)
SCK/VBUS_DETECT: P23.3 (SCK), R12.1, R13.2, U10.7 ((ADC1)PB2)
TP_IND: U4.7 (CHRG), U10.2 ((ADC3)PB4)
VADC: U1.31 (VADC)
VBUS: C2.1, D2.2 (A2), P2.A4/B9 (VBUS), P2.B4/A9 (VBUS), R12.2, U4.4 (VCC), U4.8 (CE), U4.PAD, U4.PAD2 (PAD)

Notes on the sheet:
Protection Circuit
Charge Circuit
12V Boost Circuit
Charge Indication Circuit
USB Boost Circuit
Audio Input Circuit
Amp Circuit
Filter Circuit
Powerswitch Circuit
3.3V Supply Circuit

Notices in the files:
parts and their libraries:
microbuilder: This work is placed in the public domain, and may be freely used for commercial and non-commercial work with the following conditions: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
